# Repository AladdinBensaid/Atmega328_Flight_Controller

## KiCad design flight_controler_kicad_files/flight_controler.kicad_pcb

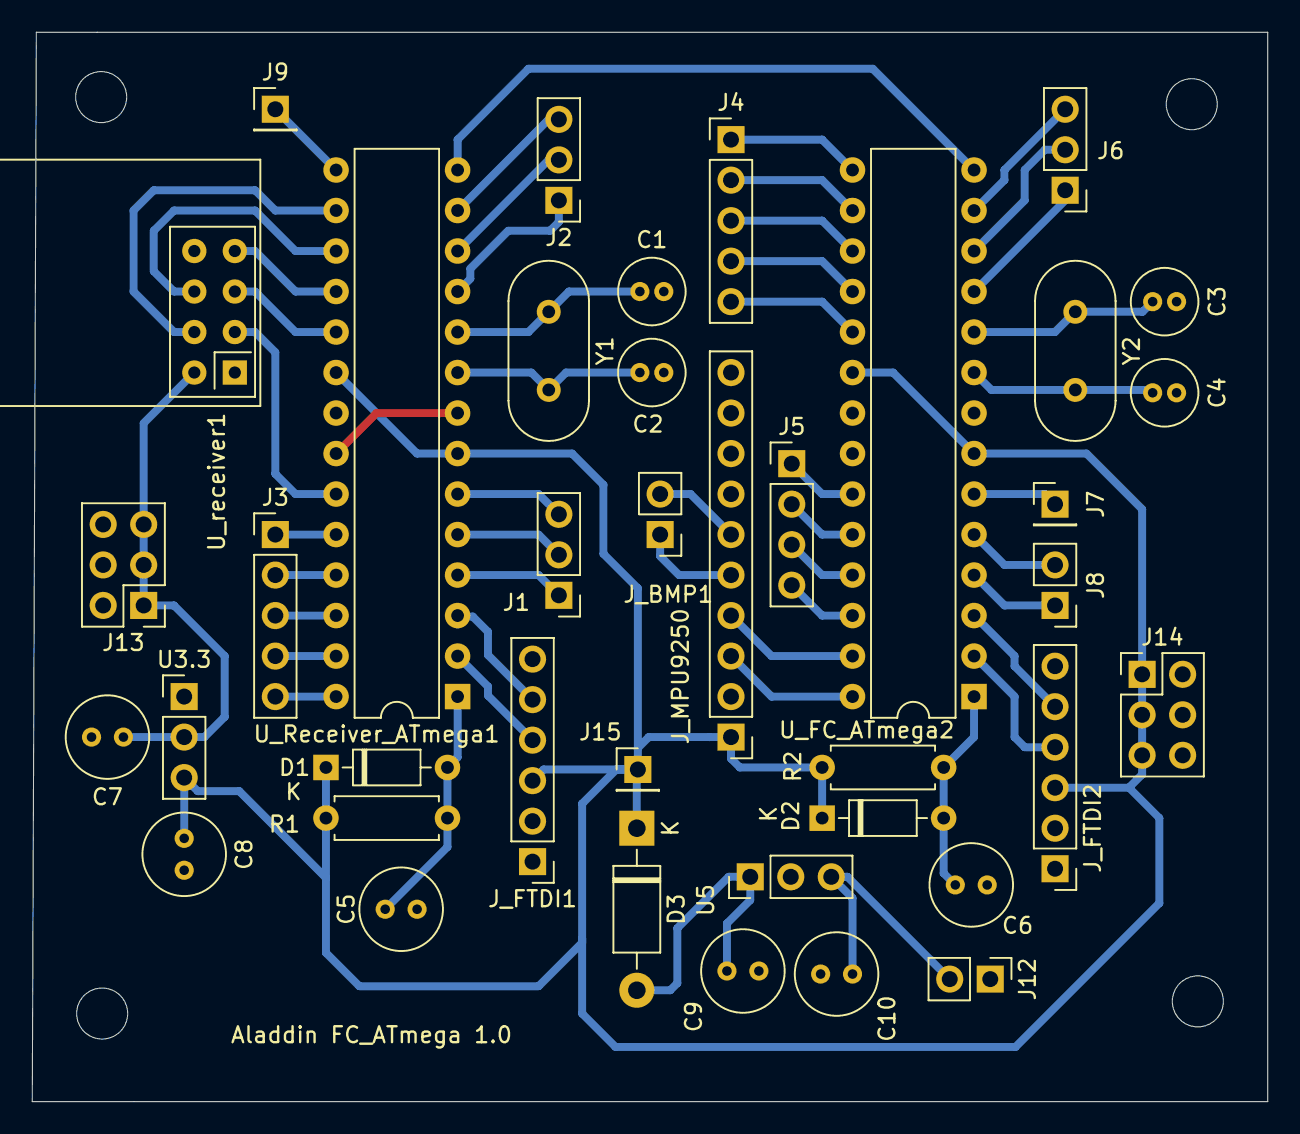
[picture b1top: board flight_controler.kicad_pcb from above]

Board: 2 copper layers, 77.5 x 67.1 mm, 39 parts (0 on the bottom side), 52 nets.

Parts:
C1, C2, C3, C4: 22pF; C_Radial_D4.0mm_H5.0mm_P1.50mm
C5, C6, C8, C10: 100nF; C_Radial_D5.0mm_H7.0mm_P2.00mm
C7, C9: 10µF; C_Radial_D5.0mm_H7.0mm_P2.00mm
D1, D2: 1N4148; D_DO-35_SOD27_P7.62mm_Horizontal
D3: 1N4001; D_DO-41_SOD81_P10.16mm_Horizontal
J1, J2, J6: Screw_Terminal_01x03; PinHeader_1x03_P2.54mm_Vertical
J3, J4: Screw_Terminal_01x05; PinHeader_1x05_P2.54mm_Vertical
J5: Screw_Terminal_01x04; PinHeader_1x04_P2.54mm_Vertical
J7, J9, J15: Screw_Terminal_01x01; PinHeader_1x01_P2.54mm_Vertical
J8, J12: Screw_Terminal_01x02; PinHeader_1x02_P2.54mm_Vertical
J13, J14: Conn_02x03_Top_Bottom; PinHeader_2x03_P2.54mm_Vertical
J_BMP1: Screw_Terminal_01x02; PinHeader_1x02_P2.54mm_Vertical
J_FTDI1, J_FTDI2: Screw_Terminal_01x06; PinHeader_1x06_P2.54mm_Vertical
J_MPU9250: Screw_Terminal_01x10; PinHeader_1x10_P2.54mm_Vertical
R1, R2: 10k; R_Axial_DIN0207_L6.3mm_D2.5mm_P7.62mm_Horizontal
U3.3: LD1117S33TR_SOT223; PinHeader_1x03_P2.54mm_Vertical
U5: LM78L05_TO92; PinHeader_1x03_P2.54mm_Vertical
U_FC_ATmega2: ATmega8L-8PU; DIP-28_W7.62mm
U_Receiver_ATmega1: ATmega8L-8PU; DIP-28_W7.62mm
U_receiver1: NRF24L01_Breakout; nRF24L01_Breakout
Y1, Y2: 16Mhz; Crystal_HC18-U_Vertical

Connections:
+3V3: C7.1, J13.1, J13.3, J13.5, U3.3.2, U_receiver1.2
+5V: C8.1, D1.1, D2.1, D3.1, J14.1, J14.3, J14.5, J15.1, J_FTDI1.3, J_FTDI2.3, J_MPU9250.1, R1.2, R2.1, U3.3.3, U_FC_ATmega2.7, U_FC_ATmega2.20, U_Receiver_ATmega1.7, U_Receiver_ATmega1.20
+12V: C10.1, J12.2, U5.3
CE: U_Receiver_ATmega1.23, U_receiver1.3
CSN: U_Receiver_ATmega1.16, U_receiver1.4
ECL: J_BMP1.2, J_MPU9250.6
EDA: J_BMP1.1, J_MPU9250.5
GND: C1.2, C2.2, C3.1, C4.1, C7.2, C8.2, C9.2, C10.2, J12.1, J13.2, J13.4, J13.6, J14.2, J14.4, J14.6, J_FTDI1.1, J_FTDI2.1, J_MPU9250.2, U3.3.1, U5.2, U_FC_ATmega2.8, U_FC_ATmega2.22, U_Receiver_ATmega1.8, U_Receiver_ATmega1.22, U_receiver1.1
MISO: U_Receiver_ATmega1.18, U_receiver1.7
MOSI: U_Receiver_ATmega1.17, U_receiver1.6
unnamed: C1.1, U_Receiver_ATmega1.10, Y1.1
unnamed: C2.1, U_Receiver_ATmega1.9, Y1.2
unnamed: C3.2, U_FC_ATmega2.10, Y2.1
unnamed: C4.2, U_FC_ATmega2.9, Y2.2
unnamed: C5.2, D1.2, R1.1, U_Receiver_ATmega1.1
unnamed: C6.2, D2.2, R2.2, U_FC_ATmega2.1
unnamed: C9.1, D3.2, U5.1
PB1: J9.1, U_Receiver_ATmega1.15
PB_1: J4.1, U_FC_ATmega2.15
PB_2: J4.2, U_FC_ATmega2.16
PB_3: J4.3, U_FC_ATmega2.17
PB_4: J4.4, U_FC_ATmega2.18
PB_5: J4.5, U_FC_ATmega2.19
PC1: J3.1, U_Receiver_ATmega1.24
PC2: J3.2, U_Receiver_ATmega1.25
PC3: J3.3, U_Receiver_ATmega1.26
PC4: J3.4, U_Receiver_ATmega1.27
PC5: J3.5, U_Receiver_ATmega1.28
PC_0: J5.1, U_FC_ATmega2.23
PC_1: J5.2, U_FC_ATmega2.24
PC_2: J5.3, U_FC_ATmega2.25
PC_3: J5.4, U_FC_ATmega2.26
PC_4: J_MPU9250.4, U_FC_ATmega2.27
PC_5: J_MPU9250.3, U_FC_ATmega2.28
PD2: J1.1, U_Receiver_ATmega1.4
PD3: J1.2, U_Receiver_ATmega1.5
PD4: J1.3, U_Receiver_ATmega1.6
PD5: J2.1, U_Receiver_ATmega1.11
PD6: J2.2, U_Receiver_ATmega1.12
PD7: J2.3, U_Receiver_ATmega1.13
PD_2: J8.1, U_FC_ATmega2.4
PD_3: J8.2, U_FC_ATmega2.5
PPM: U_FC_ATmega2.14, U_Receiver_ATmega1.14
PWM1: J7.1, U_FC_ATmega2.6
PWM2: J6.1, U_FC_ATmega2.11
PWM3: J6.2, U_FC_ATmega2.12
PWM4: J6.3, U_FC_ATmega2.13
RX: J_FTDI1.4, U_Receiver_ATmega1.2
RX2: J_FTDI2.4, U_FC_ATmega2.2
SCK: U_Receiver_ATmega1.19, U_receiver1.5
TX: J_FTDI1.5, U_Receiver_ATmega1.3
TX2: J_FTDI2.5, U_FC_ATmega2.3

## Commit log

2023-02-08 first push
